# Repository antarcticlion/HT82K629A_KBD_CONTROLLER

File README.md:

# HT82K629A_KBD_CONTROLLER
USB or PS/2 Keyboard controller board KiCad project

## Description
キーボードコントローラーIC HT82K629Aを使ったUSB PS/2両対応のコントローラー基板です。

## PCB Artwork
Rev0.4A  

## 部品表(BOM)
| Ref | Name | Qty./Note |
|:---|:---|:---|
|C1 |Capacitor 10uF | N/A |
|C2-C4 |Capacitor 0.1uF CC or MLCC | 3pcs |
|R1 |Resistor 100KR 1/4W | N/A |
|R2 |Resistor 1.5KR 1/4W | N/A |
|F1 |Ceramic resonetor 6MHz | N/A |
|D1-D3 |LED | 3pcs |
|J1 |USB B full size connector | N/A |
|J2 |Mini-DIN 6p socket | N/A |
|J3-J4 |1x20 2.54mm pitch pinheader | 2pcs |
|J5 |2x20 2.54mm pitch pinheader | N/A |
|J6-J12 |1x3 2.54mm pitch pinheader | 7pcs |
|J13-J16 |Cherry MX key switch and/or hotswap parts | 4pcs |
|J17-J20 |1x2 2.54mm pitch pinheader | 4pcs |
|J21 |JST XH 4pin socket B4B-XH-A | N/A |
|J22 |JST XH 6pin socket B6B-XH-A | N/A |
|U1 | 40pin DIP IC SOCKET 600mil | N/A |
| N/A | HT82K629A 40DIP ic | install to U1 |

## License
MIT LicenseとCreative commons CC BY-SA 4.0のデュアルライセンスとします。

https://creativecommons.org/licenses/by-sa/4.0/deed.en

https://creativecommons.org/licenses/by-sa/4.0/deed.ja

---

Copyright 2020 @antarcticlion

Permission is hereby granted, free of charge, to any person obtaining a copy of this software and associated documentation files (the "Software"), to deal in the Software without restriction, including without limitation the rights to use, copy, modify, merge, publish, distribute, sublicense, and/or sell copies of the Software, and to permit persons to whom the Software is furnished to do so, subject to the following conditions:

The above copyright notice and this permission notice shall be included in all copies or substantial portions of the Software.

THE SOFTWARE IS PROVIDED "AS IS", WITHOUT WARRANTY OF ANY KIND, EXPRESS OR IMPLIED, INCLUDING BUT NOT LIMITED TO THE WARRANTIES OF MERCHANTABILITY, FITNESS FOR A PARTICULAR PURPOSE AND NONINFRINGEMENT. IN NO EVENT SHALL THE AUTHORS OR COPYRIGHT HOLDERS BE LIABLE FOR ANY CLAIM, DAMAGES OR OTHER LIABILITY, WHETHER IN AN ACTION OF CONTRACT, TORT OR OTHERWISE, ARISING FROM, OUT OF OR IN CONNECTION WITH THE SOFTWARE OR THE USE OR OTHER DEALINGS IN THE SOFTWARE.

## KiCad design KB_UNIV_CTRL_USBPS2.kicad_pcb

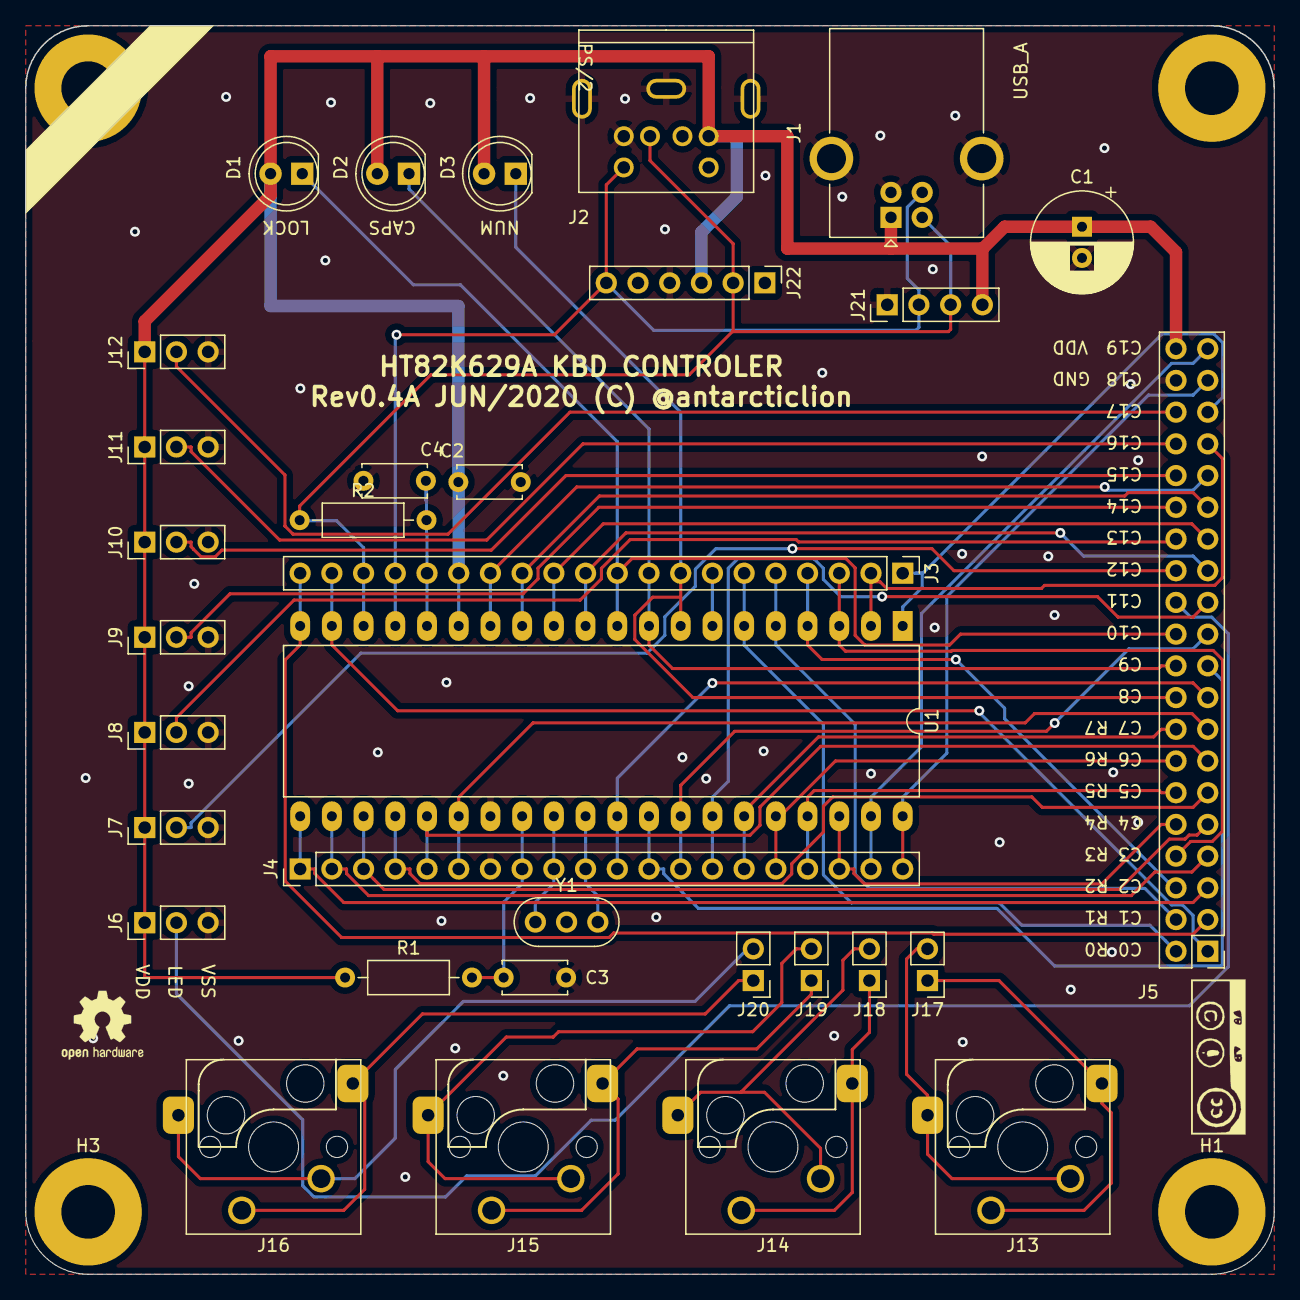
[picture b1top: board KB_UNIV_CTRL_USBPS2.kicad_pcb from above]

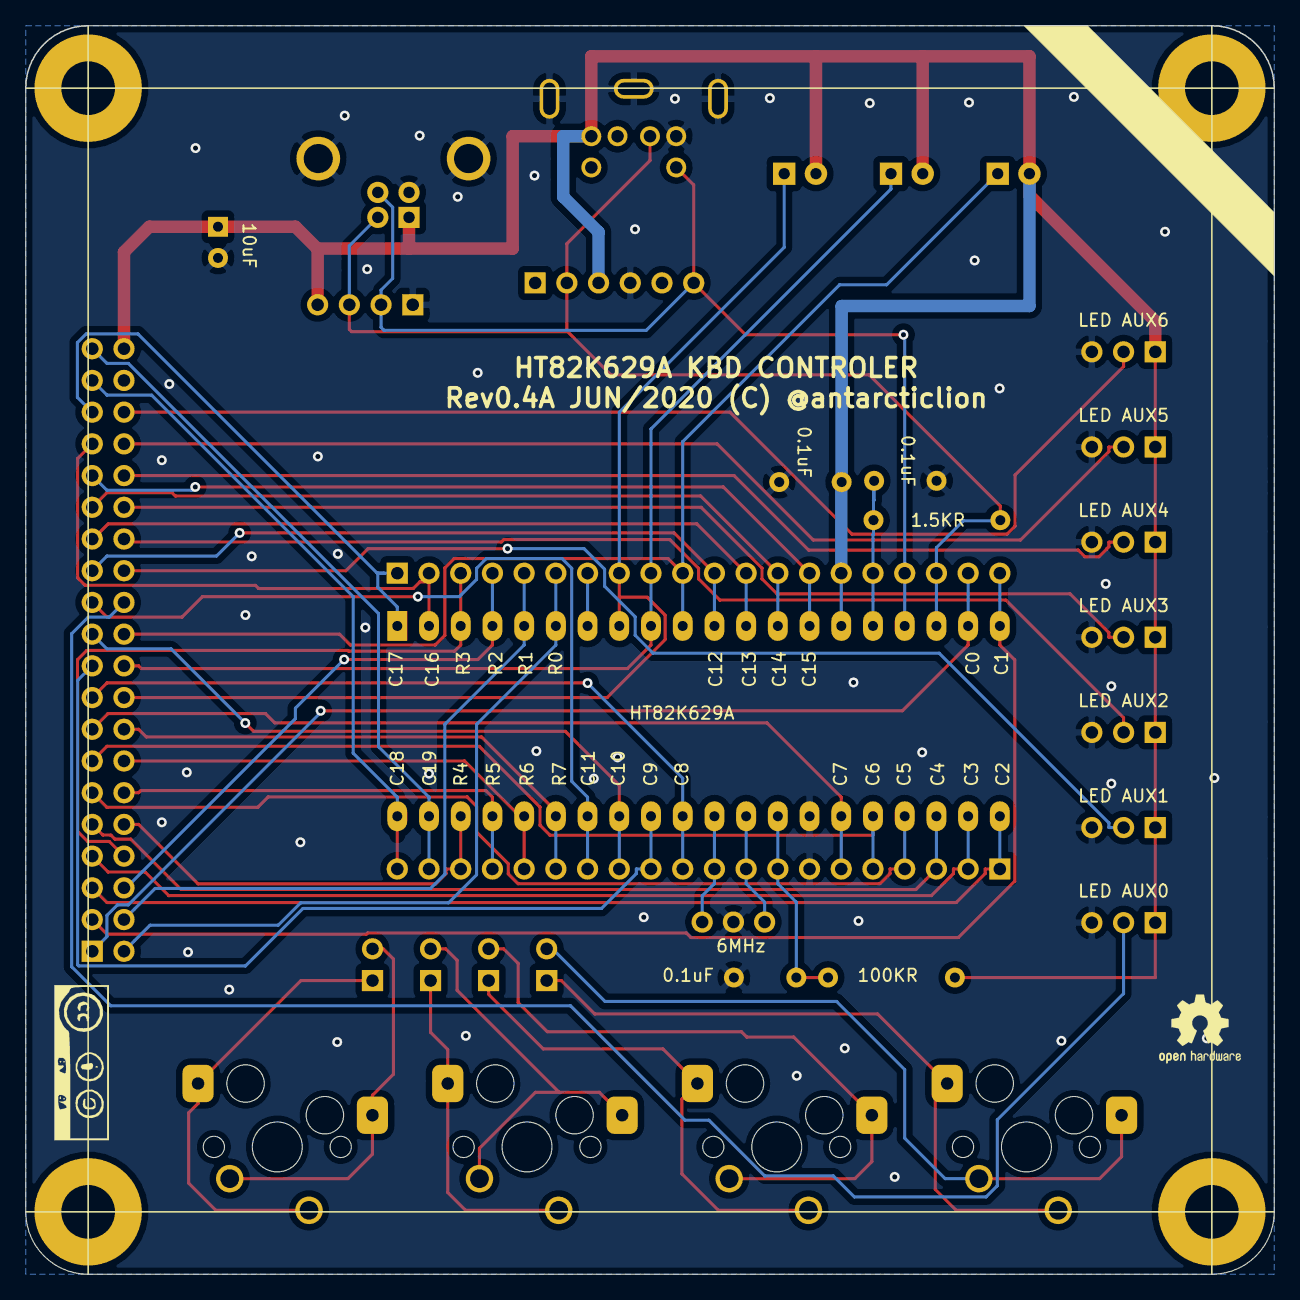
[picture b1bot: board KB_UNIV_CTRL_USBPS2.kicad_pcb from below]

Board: 2 copper layers, 100.0 x 100.0 mm, 41 parts (2 on the bottom side), 55 nets.

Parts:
C1: 10uF; CP_Radial_D8.0mm_P2.50mm
C2, C3, C4: 0.1uF; C_Disc_D5.0mm_W2.5mm_P5.00mm
D1, D2, D3: LED; LED_D5.0mm
G1, G2: LOGO; CCBYSA_LOGO2
G3, G4: OSHW-Logo2_7.3x6mm_SilkScreen
H1, H2, H3, H4: MountingHole; MountingHole_4.3mm_M4_Pad
J1: USB_A; USB_B_OST_USB-B1HSxx_Horizontal
J2: Mini-DIN-6; mini DIN 6 PCB
J3: CN_L; PinHeader_1x20_P2.54mm_Vertical
J4: CN_R; PinHeader_1x20_P2.54mm_Vertical
J5: Conn_02x20_Odd_Even; PinHeader_2x20_P2.54mm_Vertical
J6: LED AUX0; PinHeader_1x03_P2.54mm_Vertical
J7: LED AUX1; PinHeader_1x03_P2.54mm_Vertical
J8: LED AUX2; PinHeader_1x03_P2.54mm_Vertical
J9: LED AUX3; PinHeader_1x03_P2.54mm_Vertical
J10: LED AUX4; PinHeader_1x03_P2.54mm_Vertical
J11: LED AUX5; PinHeader_1x03_P2.54mm_Vertical
J12: LED AUX6; PinHeader_1x03_P2.54mm_Vertical
J13: KEY0; SW_Cherry_MX_1.00u_Hotswap
J14: KEY1; SW_Cherry_MX_1.00u_Hotswap
J15: KEY2; SW_Cherry_MX_1.00u_Hotswap
J16: KEY3; SW_Cherry_MX_1.00u_Hotswap
J17: K0; PinHeader_1x02_P2.54mm_Vertical
J18: K1; PinHeader_1x02_P2.54mm_Vertical
J19: K2; PinHeader_1x02_P2.54mm_Vertical
J20: K3; PinHeader_1x02_P2.54mm_Vertical
J21: Conn_01x04; PinHeader_1x04_P2.54mm_Vertical
J22: Conn_01x06; PinHeader_1x06_P2.54mm_Vertical
R1: 100KR; R_Axial_DIN0207_L6.3mm_D2.5mm_P10.16mm_Horizontal
R2: 1.5KR; R_Axial_DIN0207_L6.3mm_D2.5mm_P10.16mm_Horizontal
U1: HT82K629A; DIP-40_W15.24mm_LongPads
Y1: 6MHz; Resonator-3Pin_W8.0mm_H3.5mm

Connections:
#RESET: C3.1, J4.8, R1.2, U1.28
AUX0: J5.24, J6.2
AUX1: J5.26, J7.2
AUX2: J5.28, J8.2
AUX3: J5.30, J9.2
AUX4: J5.32, J10.2
AUX5: J5.34, J11.2
AUX6: J5.36, J12.2
C0: J3.19, J5.1, U1.19
C1: J3.20, J5.3, U1.20
C2: J4.1, J5.5, U1.21
C3: J4.2, J5.7, U1.22
C4: J4.3, J5.9, U1.23
C5: J4.4, J5.11, U1.24
C6: J4.5, J5.13, U1.25
C7: J4.6, J5.15, U1.26
C8: J4.11, J5.17, U1.31
C9: J4.12, J5.19, U1.32
C10: J4.13, J5.21, U1.33
C11: J4.14, J5.23, U1.34
C12: J3.11, J5.25, U1.11
C13: J3.12, J5.27, U1.12
C14: J3.13, J5.29, U1.13
C15: J3.14, J5.31, U1.14
C16: J3.2, J5.33, U1.2
C17: J3.1, J5.35, U1.1
C18: J4.20, J5.37, U1.40
C19: J4.19, J5.39, U1.39
CAPS_LED: D2.1, J3.9, J5.20, U1.9
D+: J1.3, J2.6, J3.17, J21.2, J22.6, U1.17
D-: J1.2, J2.2, J3.18, J21.3, J22.2, R2.1, U1.18
FN_SEL: J3.7, U1.7
NUM_LED: D3.1, J3.8, J5.18, U1.8
unnamed: J13.1, J17.1
unnamed: J13.2, J17.2
unnamed: J14.1, J18.1
unnamed: J14.2, J18.2
unnamed: J15.1, J19.1
unnamed: J15.2, J19.2
unnamed: J16.1, J20.1
unnamed: J16.2, J20.2
OSCI: J4.10, U1.30, Y1.3
OSCO: J4.9, U1.29, Y1.1
R0: J3.6, J5.2, U1.6
R1: J3.5, J5.4, U1.5
R2: J3.4, J5.6, U1.4
R3: J3.3, J5.8, U1.3
R4: J4.18, J5.10, U1.38
R5: J4.17, J5.12, U1.37
R6: J4.16, J5.14, U1.36
R7: J4.15, J5.16, U1.35
SCROLL_LED: D1.1, J3.10, J5.22, U1.10
V33O: C4.1, J3.16, R2.2, U1.16
VDD: C1.1, C2.1, D1.2, D2.2, D3.2, J1.1, J2.3, J3.15, J5.40, J6.1, J7.1, J8.1, J9.1, J10.1, J11.1, J12.1, J21.4, J22.3, R1.1, U1.15
VSS: C1.2, C2.2, C3.2, C4.2, J1.4, J1.5, J2.0, J2.4, J4.7, J5.38, J6.3, J7.3, J8.3, J9.3, J10.3, J11.3, J12.3, J21.1, J22.4, U1.27, Y1.2

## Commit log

2020-06-20 Initial upload
    Rev 0.4A
2020-06-20 Initial upload
    04A
